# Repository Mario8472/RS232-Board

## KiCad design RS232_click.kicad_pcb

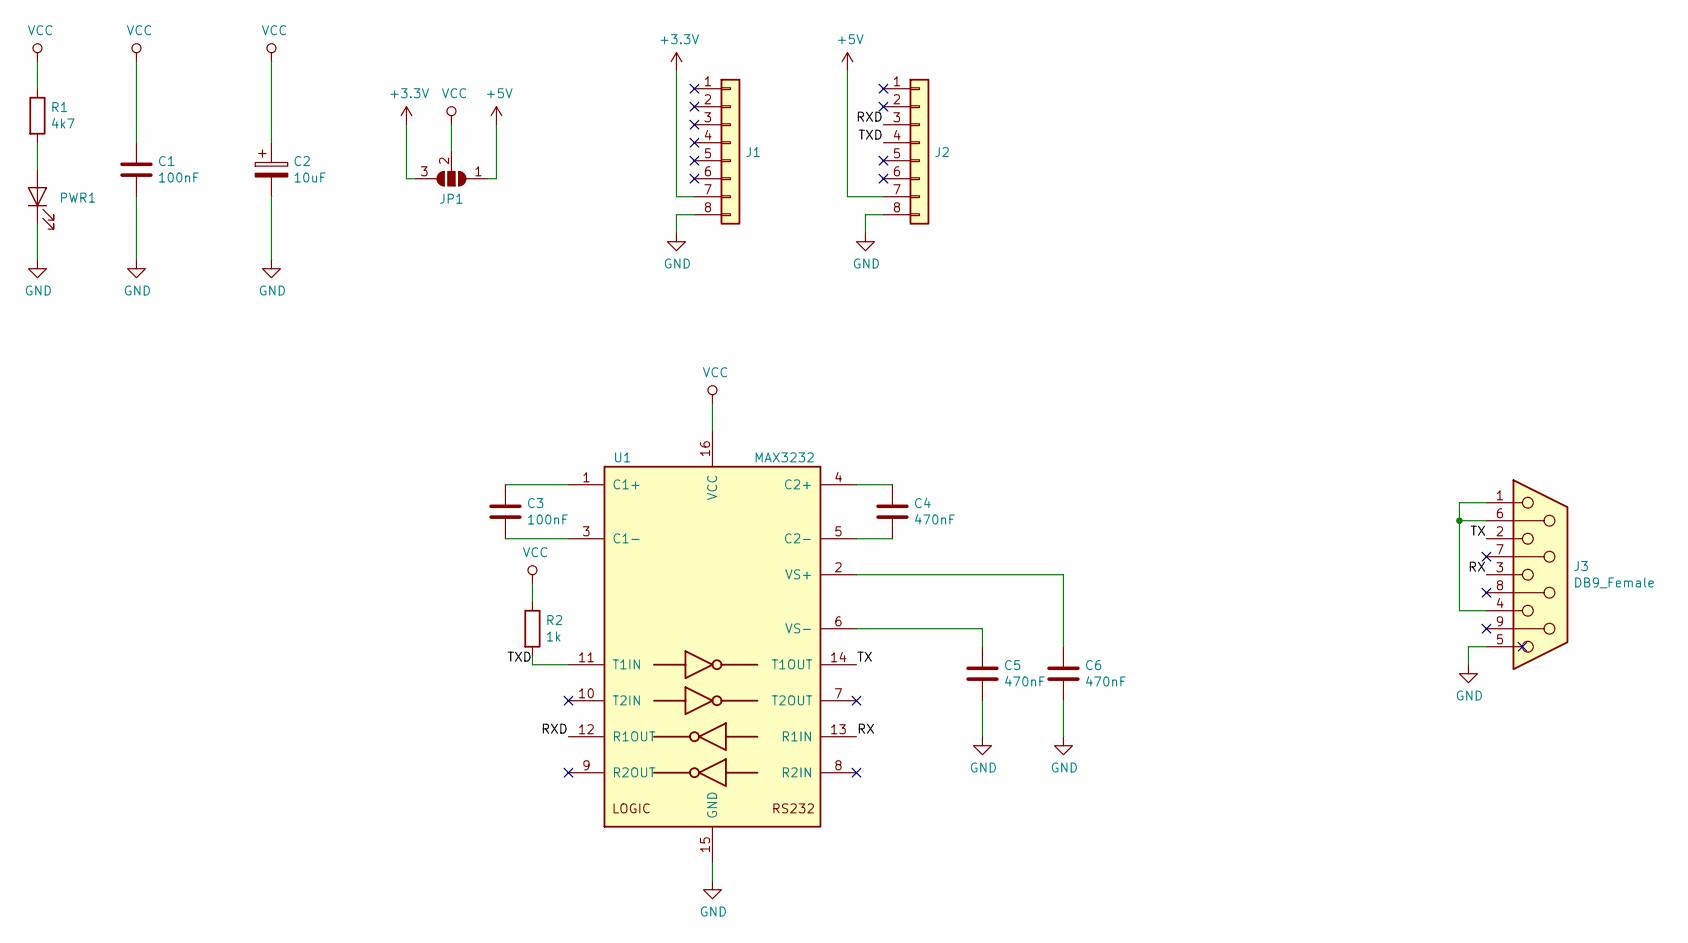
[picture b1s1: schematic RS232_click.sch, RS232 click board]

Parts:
C1, C3: 100nF; C_0805_2012Metric
C2: 10uF; CP_EIA-6032-20_AVX-F
C4, C5, C6: 470nF; C_0805_2012Metric
J1, J2: Conn_01x08; PinHeader_1x08_P2.54mm_Vertical
J3: DB9_Female; DSUB-9_Female_Horizontal_P2.77x2.84mm_EdgePinOffset4.94mm_H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
JP1: SolderJumper_3_Open; Jumper_0805
PWR1: LED; LED_0805_2012Metric
R1: 4k7; R_0805_2012Metric
R2: 1k; R_0805_2012Metric
U1: MAX3232; SOIC-16_3.9x9.9mm_P1.27mm

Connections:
+3V3: J1.7, JP1.3 (B)
+5V: J2.7, JP1.1 (A)
/RX: J3.3, U1.13 (R1IN)
/RXD: J2.3, U1.12 (R1OUT)
/TX: J3.2, U1.14 (T1OUT)
/TXD: J2.4, R2.2, U1.11 (T1IN)
GND: C1.2, C2.2, C5.2, C6.2, J1.8, J2.8, J3.5, PWR1.1 (K), U1.15 (GND)
unnamed: C3.1, U1.1 (C1+)
unnamed: C3.2, U1.3 (C1-)
unnamed: C4.1, U1.4 (C2+)
unnamed: C4.2, U1.5 (C2-)
unnamed: C5.1, U1.6 (VS-)
unnamed: C6.1, U1.2 (VS+)
unnamed: J3.1, J3.4, J3.6
unnamed: PWR1.2 (A), R1.2
VCC: C1.1, C2.1, JP1.2 (C), R1.1, R2.1, U1.16 (VCC)

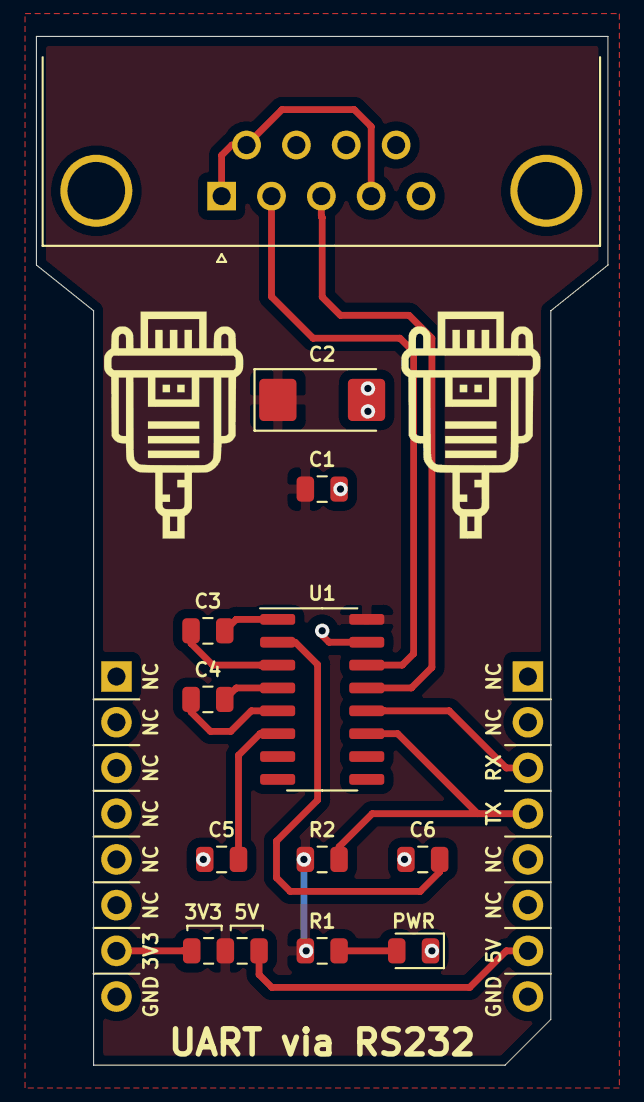
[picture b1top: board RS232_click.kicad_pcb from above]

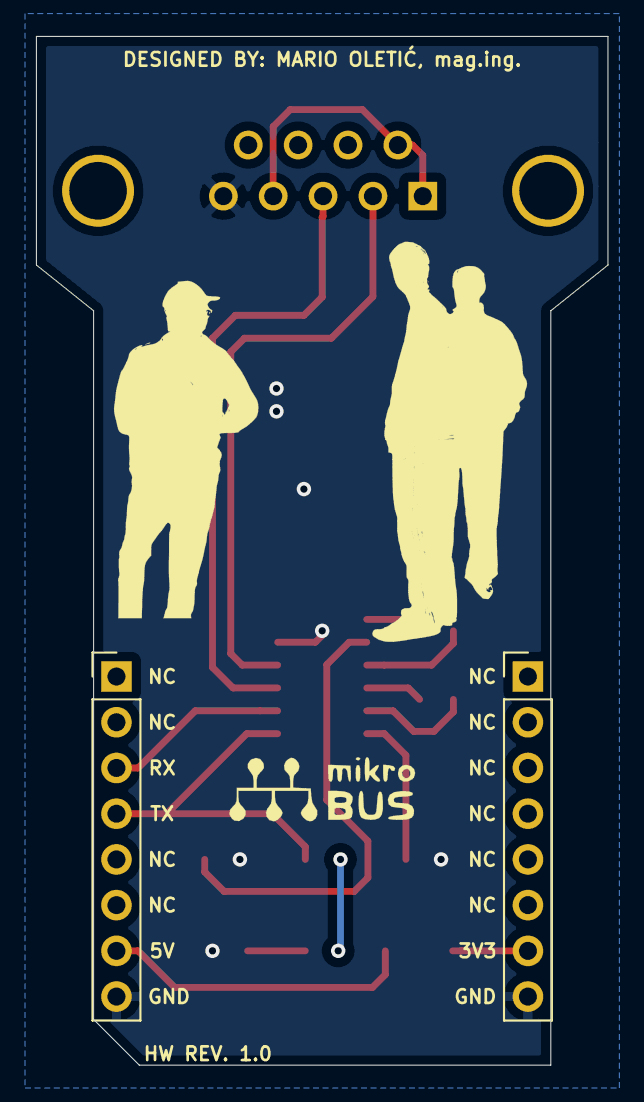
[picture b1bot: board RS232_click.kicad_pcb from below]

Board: 2 copper layers, 31.8 x 57.2 mm, 14 parts (2 on the bottom side), 16 nets.
